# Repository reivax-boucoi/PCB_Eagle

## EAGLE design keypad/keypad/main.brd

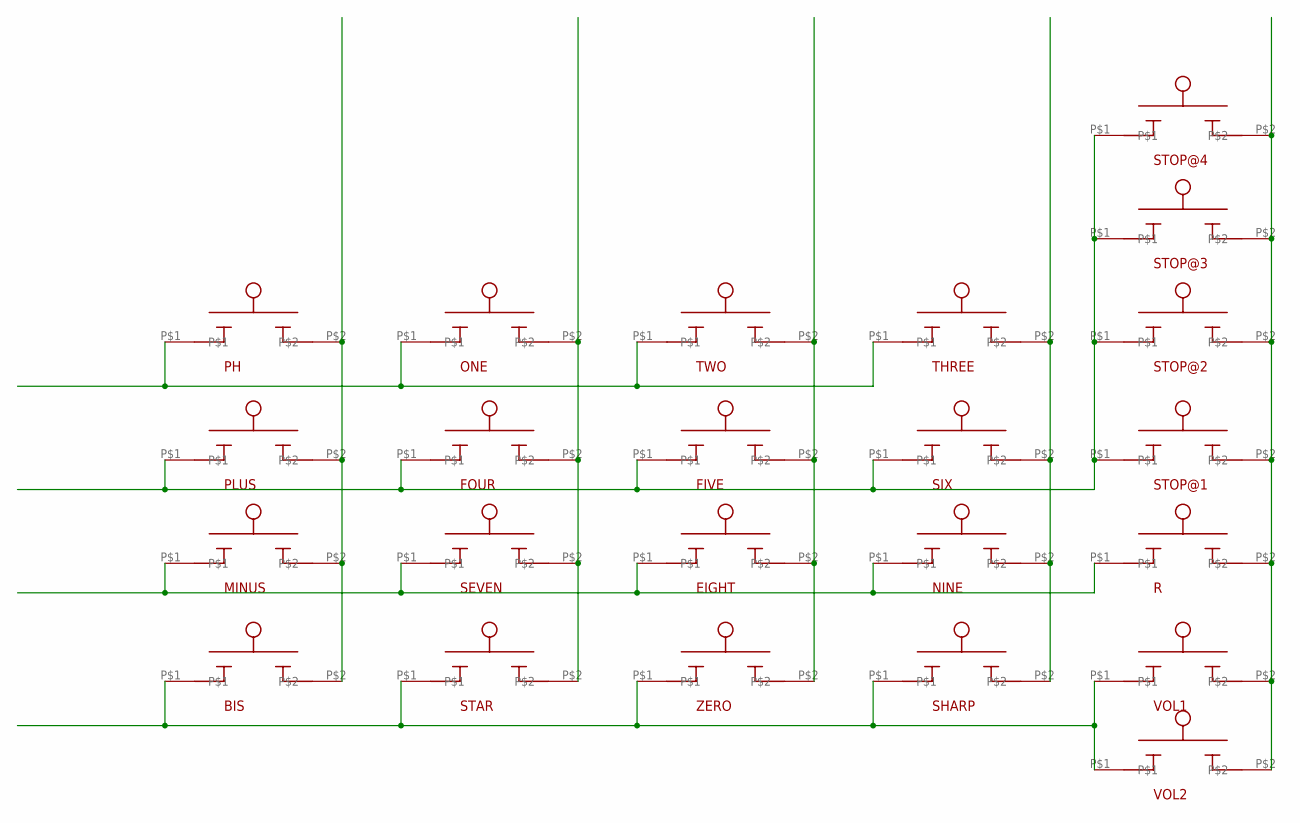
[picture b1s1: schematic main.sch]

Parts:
BIS: MEMBRANE_BUTTON
EIGHT: MEMBRANE_BUTTON
FIVE: MEMBRANE_BUTTON
FOUR: MEMBRANE_BUTTON
MINUS: MEMBRANE_BUTTON
NINE: MEMBRANE_BUTTON
ONE: MEMBRANE_BUTTON
PH: MEMBRANE_BUTTON
PLUS: MEMBRANE_BUTTON
R: MEMBRANE_BUTTON
SEVEN: MEMBRANE_BUTTON
SHARP: MEMBRANE_BUTTON
SIX: MEMBRANE_BUTTON
STAR: MEMBRANE_BUTTON
STOP@1, STOP@2, STOP@3, STOP@4: MEMBRANE_BUTTON
THREE: MEMBRANE_BUTTON
TWO: MEMBRANE_BUTTON
VOL1, VOL2: MEMBRANE_BUTTON
ZERO: MEMBRANE_BUTTON

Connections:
unnamed: ONE.P$1, PH.P$1, THREE.P$1, TWO.P$1
unnamed: FIVE.P$1, FOUR.P$1, PLUS.P$1, SIX.P$1, STOP@1.P$1, STOP@2.P$1, STOP@3.P$1, STOP@4.P$1
unnamed: EIGHT.P$1, MINUS.P$1, NINE.P$1, R.P$1, SEVEN.P$1
unnamed: BIS.P$2, MINUS.P$2, PH.P$2, PLUS.P$2
unnamed: FOUR.P$2, ONE.P$2, SEVEN.P$2, STAR.P$2
unnamed: EIGHT.P$2, FIVE.P$2, TWO.P$2, ZERO.P$2
unnamed: NINE.P$2, SHARP.P$2, SIX.P$2, THREE.P$2
unnamed: R.P$2, STOP@1.P$2, STOP@2.P$2, STOP@3.P$2, STOP@4.P$2, VOL1.P$2, VOL2.P$2
unnamed: BIS.P$1, SHARP.P$1, STAR.P$1, VOL1.P$1, VOL2.P$1, ZERO.P$1

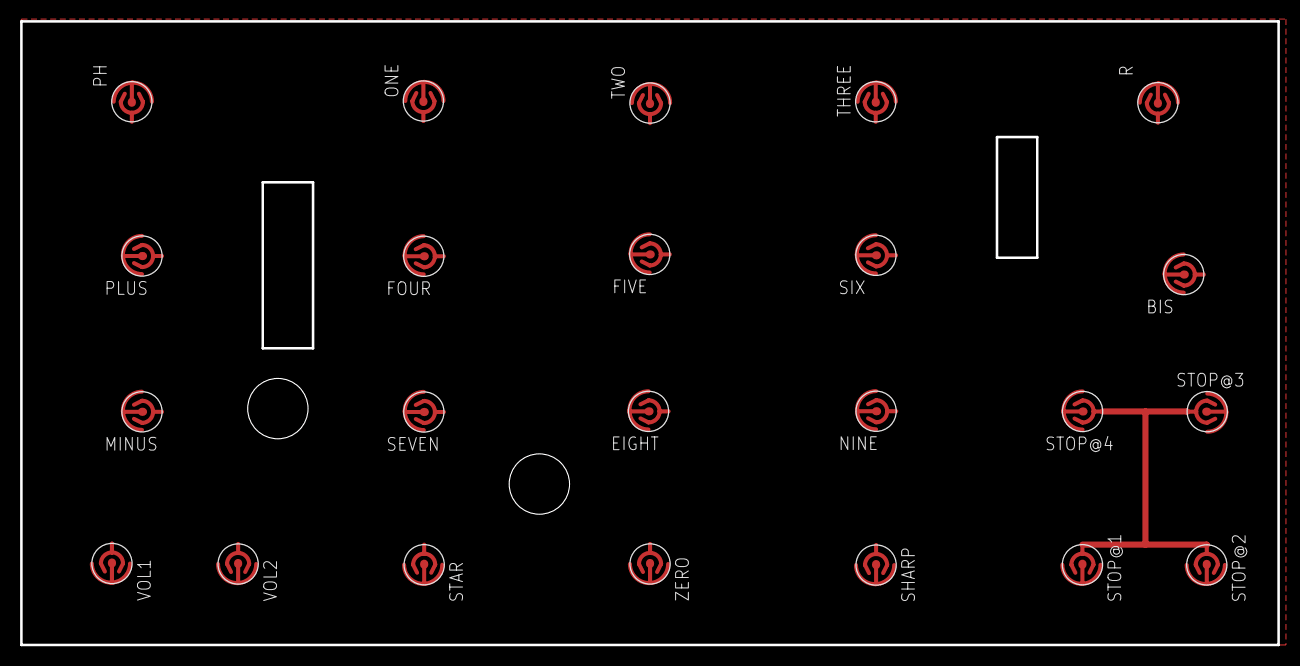
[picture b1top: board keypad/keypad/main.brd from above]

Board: 2 copper layers, 125.0 x 62.0 mm, 23 parts (0 on the bottom side), 9 nets.

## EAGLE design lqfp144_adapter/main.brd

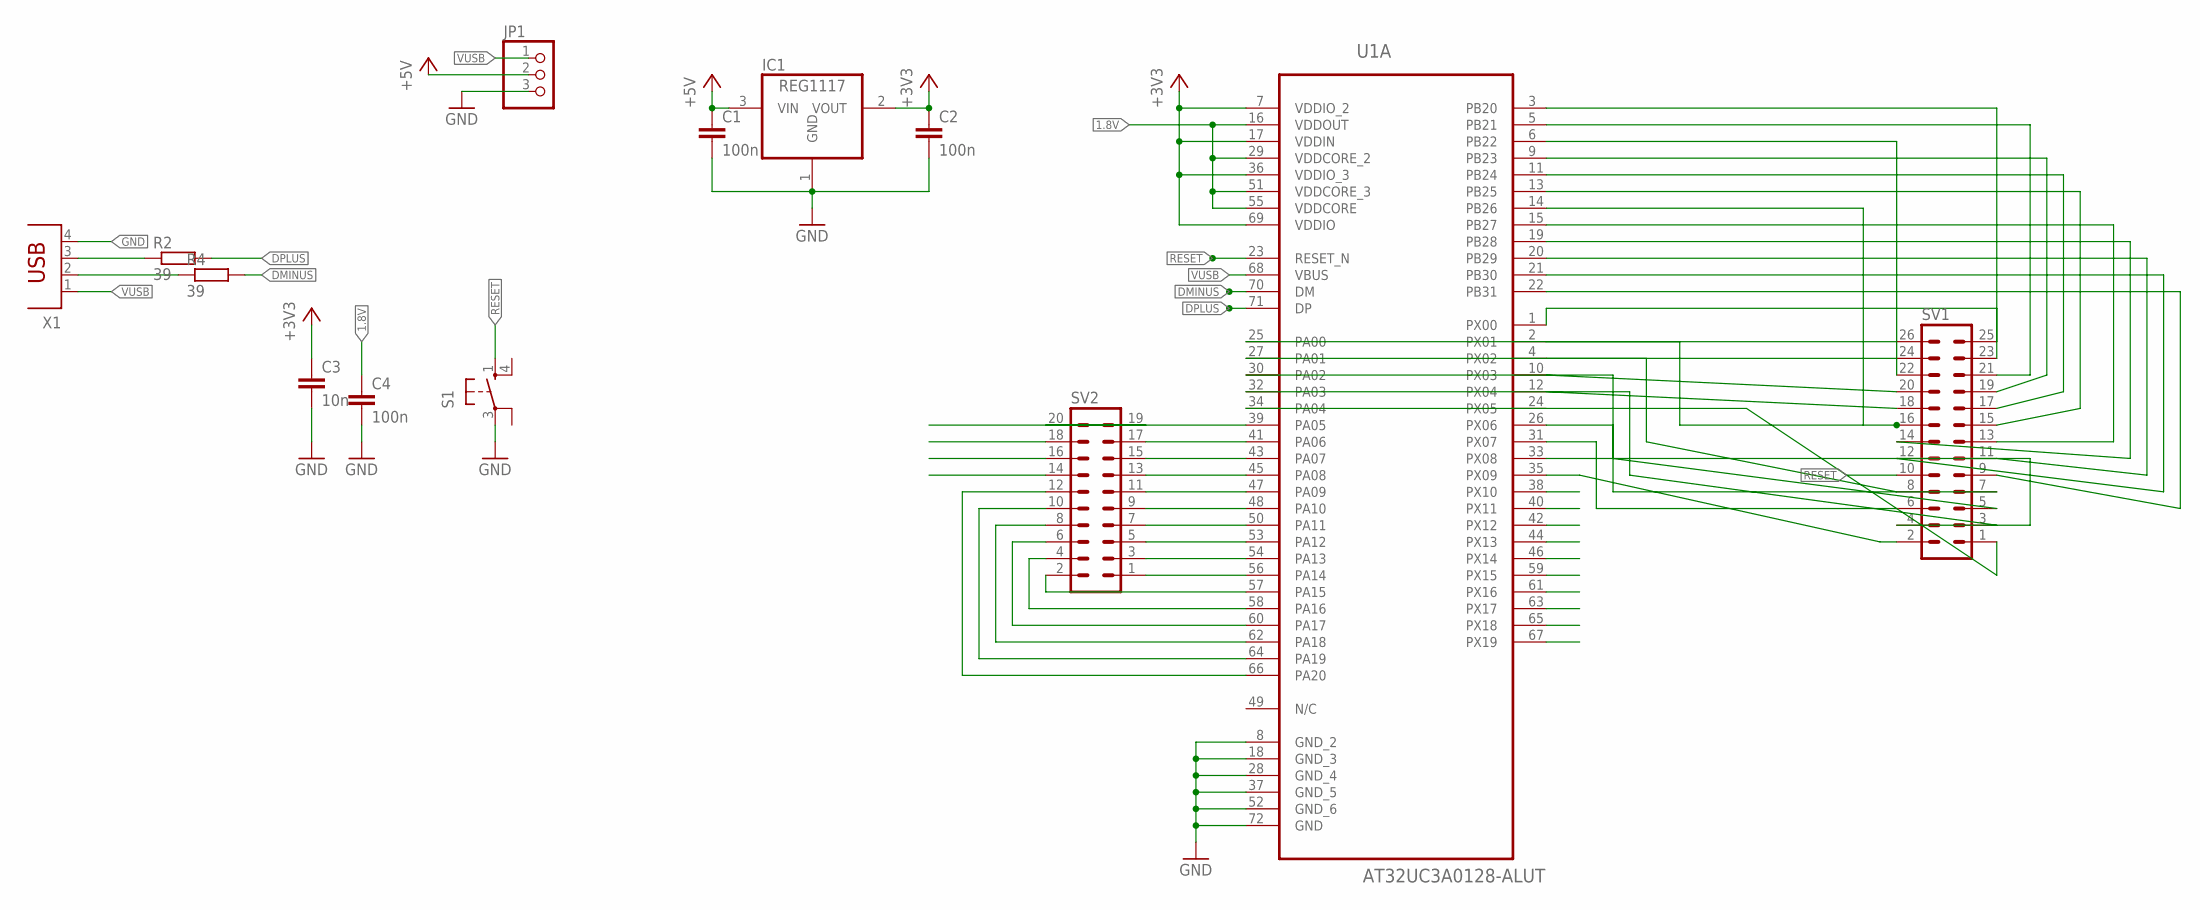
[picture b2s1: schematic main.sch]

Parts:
C1, C2, C4: 100n; C050-025X075
C3: 10n; C050-025X075
IC1: REG1117; SOT223
JP1: PINHD-1X3; 1X03
R2, R4: 39; 0207/10
S1: 10-XX; B3F-10XX
SV1: MA13-2
SV2: MA10-2
U1: AT32UC3A0128-ALUT; QFP50P2200X2200X160-144N
X1: PN61729

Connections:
1.8V: C4.1, U1.16 (VDDOUT), U1.29 (VDDCORE_2), U1.51 (VDDCORE_3), U1.55 (VDDCORE)
+3V3: C2.1, C3.1, IC1.2 (VOUT), U1.7 (VDDIO_2), U1.17 (VDDIN), U1.36 (VDDIO_3), U1.69 (VDDIO)
+5V: C1.1, IC1.3 (VIN), JP1.2
B$1: SV2.14, SV2.16, SV2.18, SV2.19, U1.38 (PX10), U1.40 (PX11), U1.42 (PX12), U1.44 (PX13), U1.46 (PX14), U1.59 (PX15), U1.61 (PX16), U1.63 (PX17), U1.65 (PX18), U1.67 (PX19)
DMINUS: R4.2, U1.70 (DM)
DPLUS: R2.2, U1.71 (DP)
GND: C1.2, C2.2, C3.2, C4.2, IC1.1 (GND), JP1.3, S1.3, U1.8 (GND_2), U1.18 (GND_3), U1.28 (GND_4), U1.37 (GND_5), U1.52 (GND_6), U1.72 (GND), X1.4
unnamed: SV1.25, U1.1 (PX00)
unnamed: SV1.26, U1.2 (PX01)
unnamed: SV1.23, U1.3 (PB20)
unnamed: SV1.21, U1.5 (PB21)
unnamed: SV1.24, U1.4 (PX02)
unnamed: SV1.20, U1.10 (PX03)
unnamed: SV1.22, U1.6 (PB22)
unnamed: SV1.19, U1.9 (PB23)
unnamed: SV1.17, U1.11 (PB24)
unnamed: SV1.18, U1.12 (PX04)
unnamed: SV1.15, U1.13 (PB25)
unnamed: SV1.16, U1.14 (PB26), U1.25 (PA00)
unnamed: SV1.13, U1.15 (PB27)
unnamed: SV1.14, U1.19 (PB28)
unnamed: SV1.11, U1.20 (PB29)
unnamed: SV1.12, U1.21 (PB30)
unnamed: SV1.9, U1.22 (PB31)
unnamed: SV1.7, U1.26 (PX06)
unnamed: SV1.8, U1.27 (PA01)
unnamed: SV1.5, U1.30 (PA02)
unnamed: SV1.3, U1.32 (PA03)
unnamed: SV1.1, U1.34 (PA04)
unnamed: SV1.6, U1.31 (PX07)
unnamed: SV1.4, U1.33 (PX08)
unnamed: SV1.2, U1.35 (PX09)
unnamed: R2.1, X1.3
unnamed: SV2.12, U1.66 (PA20)
unnamed: R4.1, X1.2
unnamed: SV2.10, U1.64 (PA19)
unnamed: SV2.8, U1.62 (PA18)
unnamed: SV2.6, U1.60 (PA17)
unnamed: SV2.4, U1.58 (PA16)
unnamed: SV2.2, U1.57 (PA15)
unnamed: SV2.1, U1.56 (PA14)
unnamed: SV2.3, U1.54 (PA13)
unnamed: SV2.5, U1.53 (PA12)
unnamed: SV2.7, U1.50 (PA11)
unnamed: SV2.9, U1.48 (PA10)
unnamed: SV2.11, U1.47 (PA09)
unnamed: SV2.13, U1.45 (PA08)
unnamed: SV2.15, U1.43 (PA07)
unnamed: SV2.17, U1.41 (PA06)
unnamed: SV2.20, U1.39 (PA05)
RESET: S1.1 (S), SV1.10, U1.23 (RESET_N)
VDDANA: U1.81 (VDDANA)
VDDCORE: U1.138 (VDDCORE)
VDDIO: U1.116 (VDDIO)
VDDIO_2: U1.92 (VDDIO_2)
VDDIO_3: U1.93 (VDDIO_3)
VDDIO_4: U1.108 (VDDIO_4)
VDDPLL: U1.84 (VDDPLL)
VUSB: JP1.1, U1.68 (VBUS), X1.1

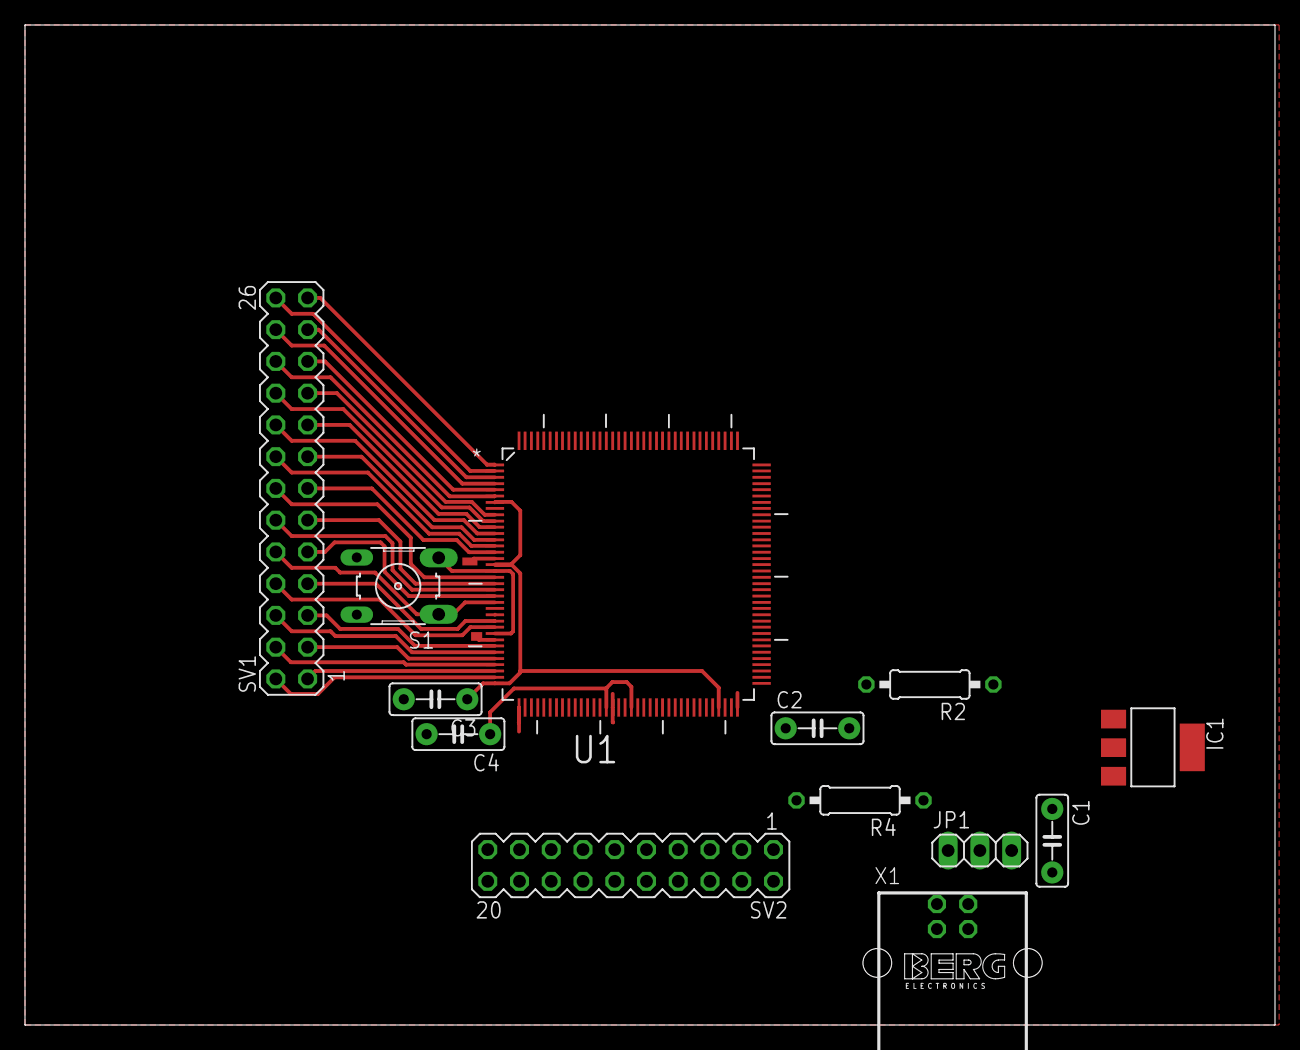
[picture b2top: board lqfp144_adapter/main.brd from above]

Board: 2 copper layers, 100.0 x 80.0 mm, 13 parts (0 on the bottom side), 52 nets.

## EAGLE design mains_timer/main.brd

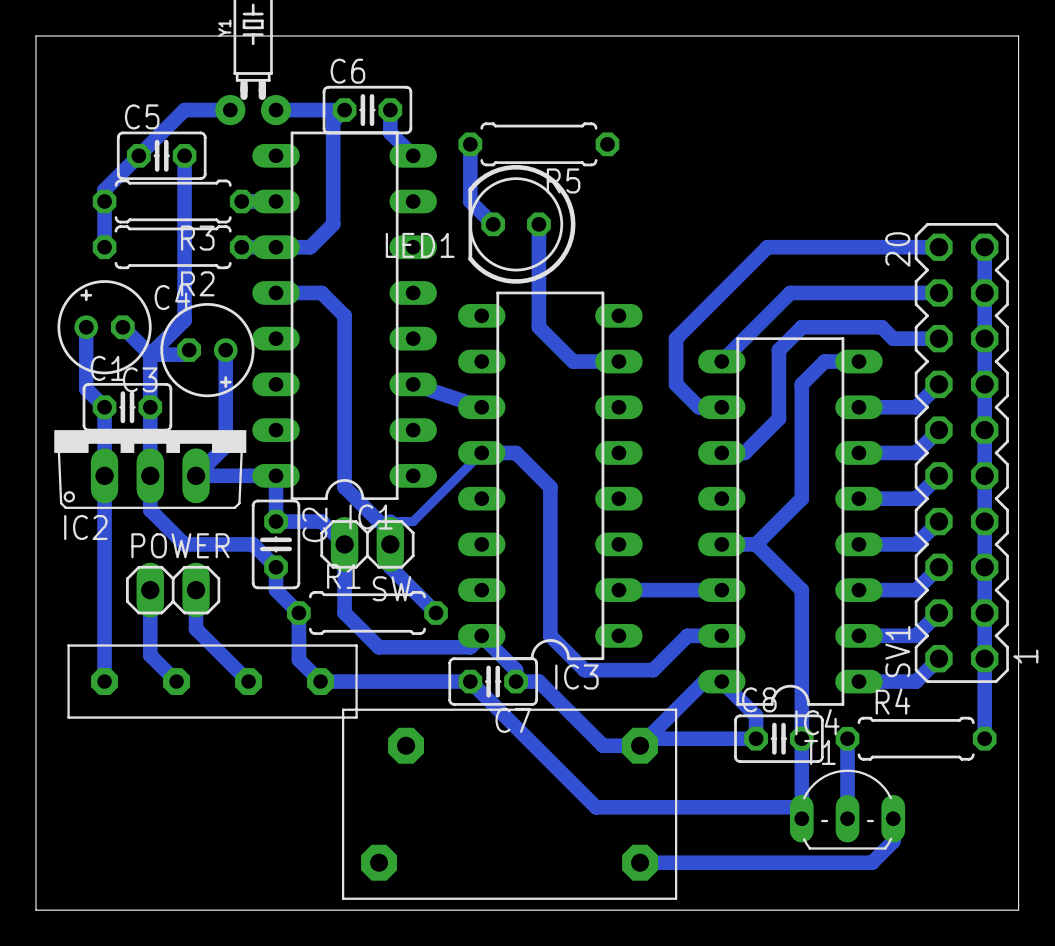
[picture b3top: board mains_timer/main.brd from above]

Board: 2 copper layers, 54.6 x 48.6 mm, 25 parts (0 on the bottom side), 26 nets.

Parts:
C1: 100u; C025-025X050
C2, C7, C8: 100n; C025-025X050
C3: 100u; E2-5
C4: 100n; E2-5
C5, C6: 33p; C025-025X050
IC1, IC3: 4060N; DIL16
IC2: 7812TV; TO220V
IC4: 4017N; DIL16
LED1: LED5MM
POWER: 1X02
R1: 22k; 0207/7
R2: 10M; 0207/7
R3: 330k; 0207/7
R4: 0207/7
R5: 500; 0207/7
SV1: MA10-2
SW: 1X02
T1: 2N2222; TO92-EBC-OVAL
U$2: KBP205GK; KBP205G
U$3: 835-1A_RELAY12V; 835-1A_RELAY_12V
Y1: 32.768kHz; CRYSTAL-PTH-2X6-CYL

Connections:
12V: C2.1, C3.+, C7.1, C8.1, IC1.16, IC2.3, IC3.16, IC4.16, SW.2, U$3.P$1
GND: C1.2, C2.2, C3.-, C4.-, C5.2, C6.2, C7.2, C8.2, IC1.8, IC2.2, IC3.8, IC4.8, IC4.13, R1.1, R5.1, T1.E, U$2.-
unnamed: POWER.2, U$2.AC@2
unnamed: POWER.1, U$2.AC@1
unnamed: IC1.12, IC3.12, IC4.15, R1.2, SW.1
unnamed: IC1.10, R3.1
unnamed: C6.1, IC1.11, R2.1, Y1.2
unnamed: IC1.3, IC3.11
unnamed: C5.1, R2.2, R3.2, Y1.1
unnamed: IC3.2, IC4.14
unnamed: IC4.11, SV1.16
unnamed: IC4.9, SV1.18
unnamed: IC4.6, SV1.12
unnamed: IC4.5, SV1.10
unnamed: IC4.1, SV1.2
unnamed: IC4.10, SV1.20
unnamed: IC4.7, SV1.14
unnamed: IC4.4, SV1.8
unnamed: IC4.2, SV1.4
unnamed: IC4.3, SV1.6
unnamed: R4.2, SV1.1, SV1.3, SV1.5, SV1.7, SV1.9, SV1.11, SV1.13, SV1.15, SV1.17, SV1.19
unnamed: R4.1, T1.B
unnamed: T1.C, U$3.P$2
unnamed: LED1.K, R5.2
unnamed: IC3.7, LED1.A
VDD: C1.1, C4.+, IC2.1, U$2.+

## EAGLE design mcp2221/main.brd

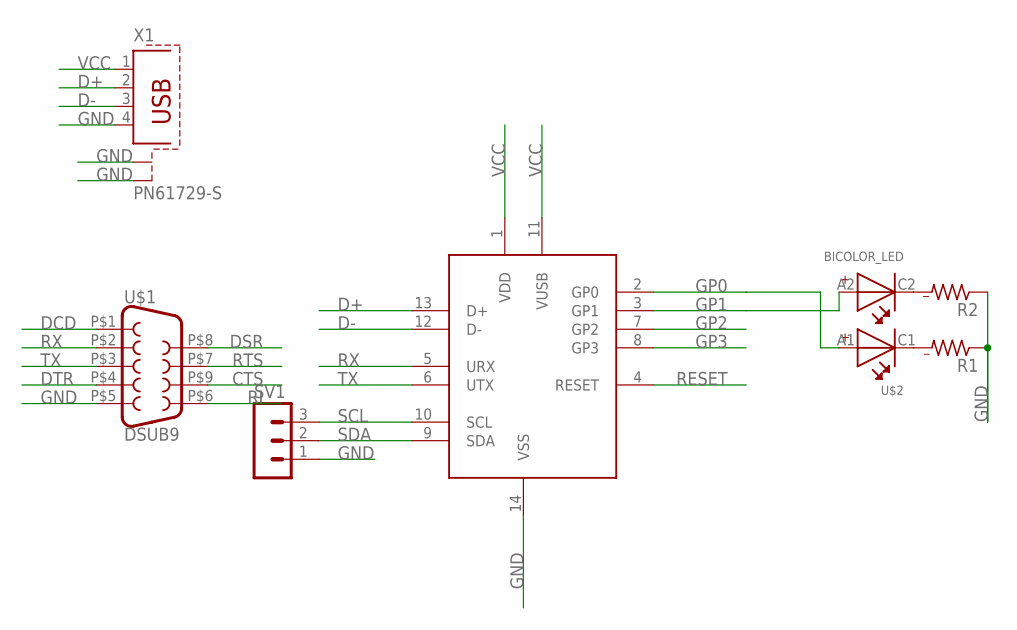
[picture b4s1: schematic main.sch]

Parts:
BR1: MCP2221A; DIP14
R1, R2: R-US_M0805; M0805
SV1: MA03-1
U$1: DSUB9; DSUB9_EDGECARD
U$2: BICOLOR_LED
X1: PN61729-S

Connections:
CTS: U$1.P$9 (CTS)
D+: BR1.13 (D+), X1.2
D-: BR1.12 (D-), X1.3
DCD: U$1.P$1 (DCD)
DSR: U$1.P$8 (DSR)
DTR: U$1.P$4 (DTR)
GND: BR1.14 (VSS), R1.1, R2.1, SV1.1, U$1.P$5 (GND), X1.4, X1.S1, X1.S2
GP0: BR1.2 (GP0), U$2.A1
GP1: BR1.3 (GP1), U$2.A2
GP2: BR1.7 (GP2)
GP3: BR1.8 (GP3)
unnamed: R1.2, U$2.C1
unnamed: R2.2, U$2.C2
RESET: BR1.4 (RESET)
RI: U$1.P$6 (RI)
RTS: U$1.P$7 (RTS)
RX: BR1.5 (URX), U$1.P$2 (RXD)
SCL: BR1.10 (SCL), SV1.3
SDA: BR1.9 (SDA), SV1.2
TX: BR1.6 (UTX), U$1.P$3 (TXD)
VCC: BR1.1 (VDD), BR1.11 (VUSB), X1.1

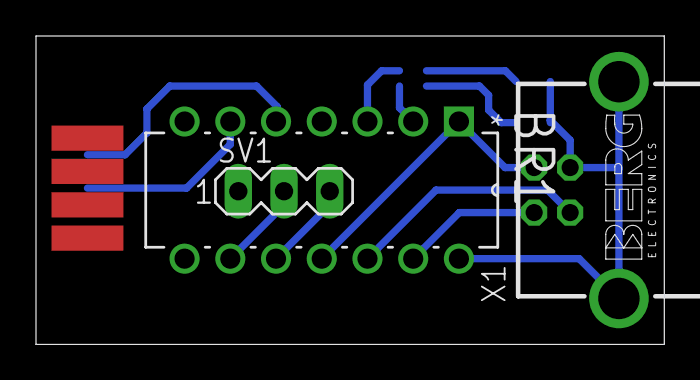
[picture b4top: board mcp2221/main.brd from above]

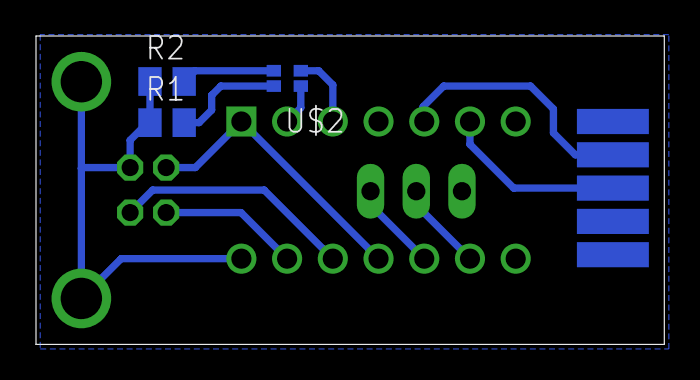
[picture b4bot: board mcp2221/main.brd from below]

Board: 2 copper layers, 34.9 x 17.1 mm, 7 parts (4 on the bottom side), 12 nets.

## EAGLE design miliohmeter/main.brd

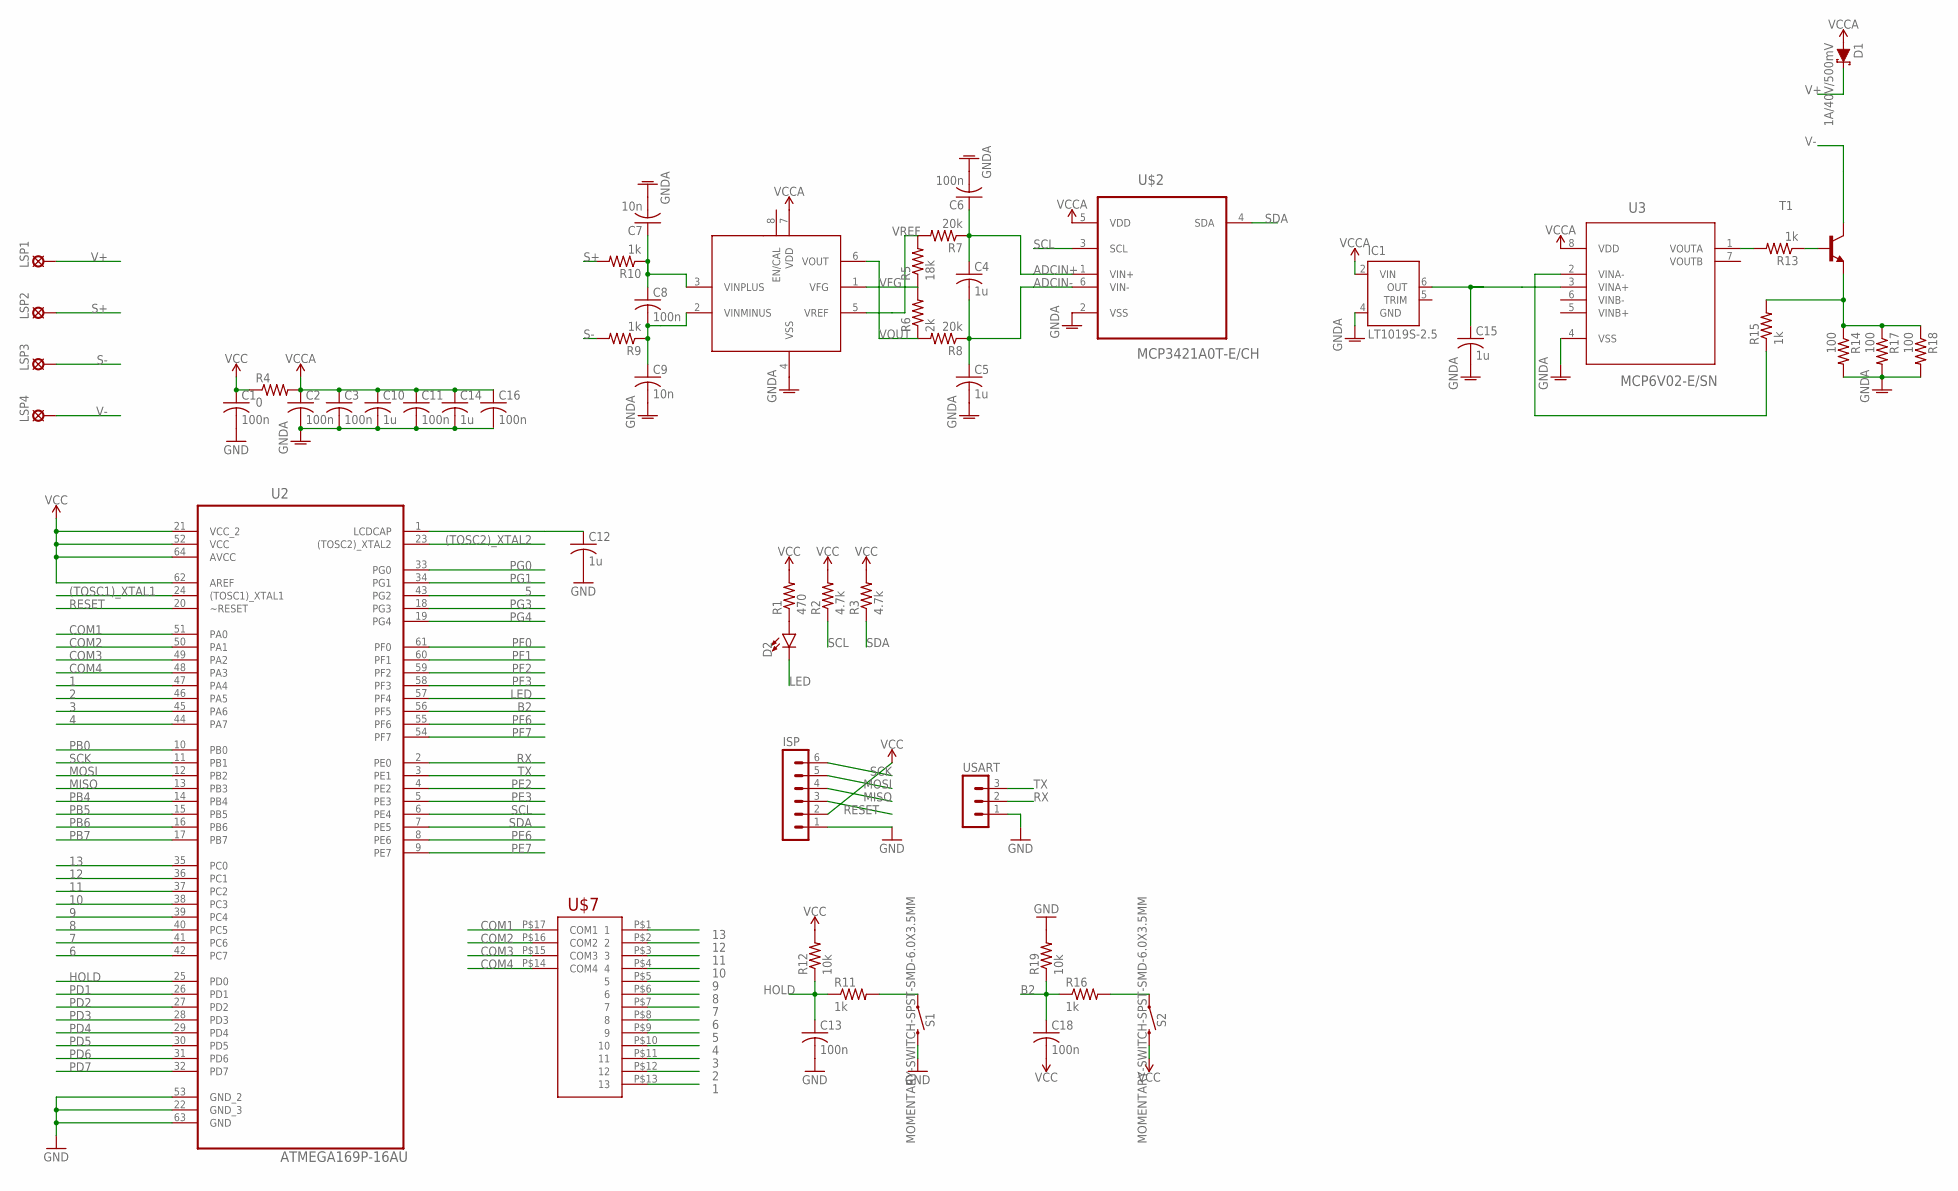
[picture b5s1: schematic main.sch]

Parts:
C1, C2, C3, C6, C8, C11, C13, C16, C18: 100n; C0603
C4, C5, C10, C12, C14, C15: 1u; C0603
C7, C9: 10n; C0603
D1: 1A/40V/500mV; SMA-DIODE
D2: LED5MM; LED_5MM
IC1: LT1019S-2.5; SOIC8
ISP: MA06-1
LSP1, LSP2, LSP3, LSP4: MCS08
R1: 470; R0603
R2, R3: 4.7k; R0603
R4: 0; 0309/12
R5: 18k; R0603
R6: 2k; R0603
R7, R8: 20k; R0603
R9, R10, R11, R13, R15, R16: 1k; R0603
R12, R19: 10k; R0603
R14, R17, R18: 100; R0603
S1, S2: MOMENTARY-SWITCH-SPST-SMD-6.0X3.5MM; TACTILE_SWITCH_SMD_6.0X3.5MM
T1: MMBT3904LT1-NPN-SOT23-BEC; SOT23-BEC
U2: ATMEGA169P-16AU; QFP80P1600X1600X120-64N
U3: MCP6V02-E/SN; SOIC127P600X175-8N
U$2: MCP3421A0T-E/CH; SOT95P270X145-6N
U$3: MCP6N11; SOIC8
U$7: GDC0570_LCD
USART: MA03-1

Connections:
1: U2.47 (PA4), U$7.P$13 (13)
2: U2.46 (PA5), U$7.P$12 (12)
3: U2.45 (PA6), U$7.P$11 (11)
4: U2.44 (PA7), U$7.P$10 (10)
5: U2.43 (PG2), U$7.P$9 (9)
6: U2.42 (PC7), U$7.P$8 (8)
7: U2.41 (PC6), U$7.P$7 (7)
8: U2.40 (PC5), U$7.P$6 (6)
9: U2.39 (PC4), U$7.P$5 (5)
10: U2.38 (PC3), U$7.P$4 (4)
11: U2.37 (PC2), U$7.P$3 (3)
12: U2.36 (PC1), U$7.P$2 (2)
13: U2.35 (PC0), U$7.P$1 (1)
ADCIN+: C4.1, C6.1, R7.1, U$2.1 (VIN+)
ADCIN-: C4.2, C5.1, R8.1, U$2.6 (VIN-)
B2: C18.1, R16.1, R19.1, U2.56 (PF5)
COM1: U2.51 (PA0), U$7.P$17 (COM1)
COM2: U2.50 (PA1), U$7.P$16 (COM2)
COM3: U2.49 (PA2), U$7.P$15 (COM3)
COM4: U2.48 (PA3), U$7.P$14 (COM4)
GND: C1.2, C12.2, C13.2, ISP.1, R19.2, S1.2, U2.22 (GND_3), U2.53 (GND_2), U2.63 (GND), USART.1; also elsewhere on the board
GNDA: C2.2, C3.2, C5.2, C6.2, C7.2, C9.2, C10.2, C11.2, C14.2, C15.2, C16.2, IC1.4 (GND), R14.2, R17.2, R18.2, U3.4 (VSS), U$2.2 (VSS), U$3.4 (VSS)
HOLD: C13.1, R11.1, R12.1, U2.25 (PD0)
LCDCAP: C12.1, U2.1 (LCDCAP)
LED: D2.K (C), U2.57 (PF4)
MISO: ISP.4, U2.13 (PB3)
MOSI: ISP.5, U2.12 (PB2)
N1: R11.2, S1.1
N2: R16.2, S2.1
unnamed: C15.1, IC1.6 (OUT), U3.3 (VINA+)
unnamed: R14.1, R15.2, R17.1, R18.1, T1.E
unnamed: C8.2, C9.1, R9.1, U$3.2 (VINMINUS)
unnamed: C7.1, C8.1, R10.1, U$3.3 (VINPLUS)
unnamed: D2.A, R1.1
unnamed: R13.2, U3.1 (VOUTA)
unnamed: R13.1, T1.B
unnamed: R15.1, U3.2 (VINA-)
PB0: U2.10 (PB0)
PB4: U2.14 (PB4)
PB5: U2.15 (PB5)
PB6: U2.16 (PB6)
PB7: U2.17 (PB7)
PD1: U2.26 (PD1)
PD2: U2.27 (PD2)
PD3: U2.28 (PD3)
PD4: U2.29 (PD4)
PD5: U2.30 (PD5)
PD6: U2.31 (PD6)
PD7: U2.32 (PD7)
PE2: U2.4 (PE2)
PE3: U2.5 (PE3)
PE6: U2.8 (PE6)
PE7: U2.9 (PE7)
PF0: U2.61 (PF0)
PF1: U2.60 (PF1)
PF2: U2.59 (PF2)
PF3: U2.58 (PF3)
PF6: U2.55 (PF6)
PF7: U2.54 (PF7)
PG0: U2.33 (PG0)
PG1: U2.34 (PG1)
PG3: U2.18 (PG3)
PG4: U2.19 (PG4)
RESET: ISP.3, U2.20 (~RESET)
RX: U2.2 (PE0), USART.2; also elsewhere on the board
S+: LSP2.MP, R10.2
S-: LSP3.MP, R9.2
SCK: ISP.6, U2.11 (PB1)
SCL: R2.1, U2.6 (PE4), U$2.3 (SCL)
SDA: R3.1, U2.7 (PE5), U$2.4 (SDA)
TX: U2.3 (PE1), USART.3; also elsewhere on the board
V+: D1.C, LSP1.MP
V-: LSP4.MP, T1.C
VCC: C1.1, C18.2, ISP.2, R1.2, R2.2, R3.2, R4.1, R12.2, S2.2, U2.21 (VCC_2), U2.52 (VCC), U2.62 (AREF), U2.64 (AVCC); also elsewhere on the board
VCCA: C2.1, C3.1, C10.1, C11.1, C14.1, C16.1, D1.A, IC1.2 (VIN), R4.2, U3.8 (VDD), U$2.5 (VDD), U$3.7 (VDD)
VFG: R5.1, R6.2, U$3.1 (VFG)
VOUT: R6.1, R8.2, U$3.6 (VOUT)
VREF: R5.2, R7.2, U$3.5 (VREF)

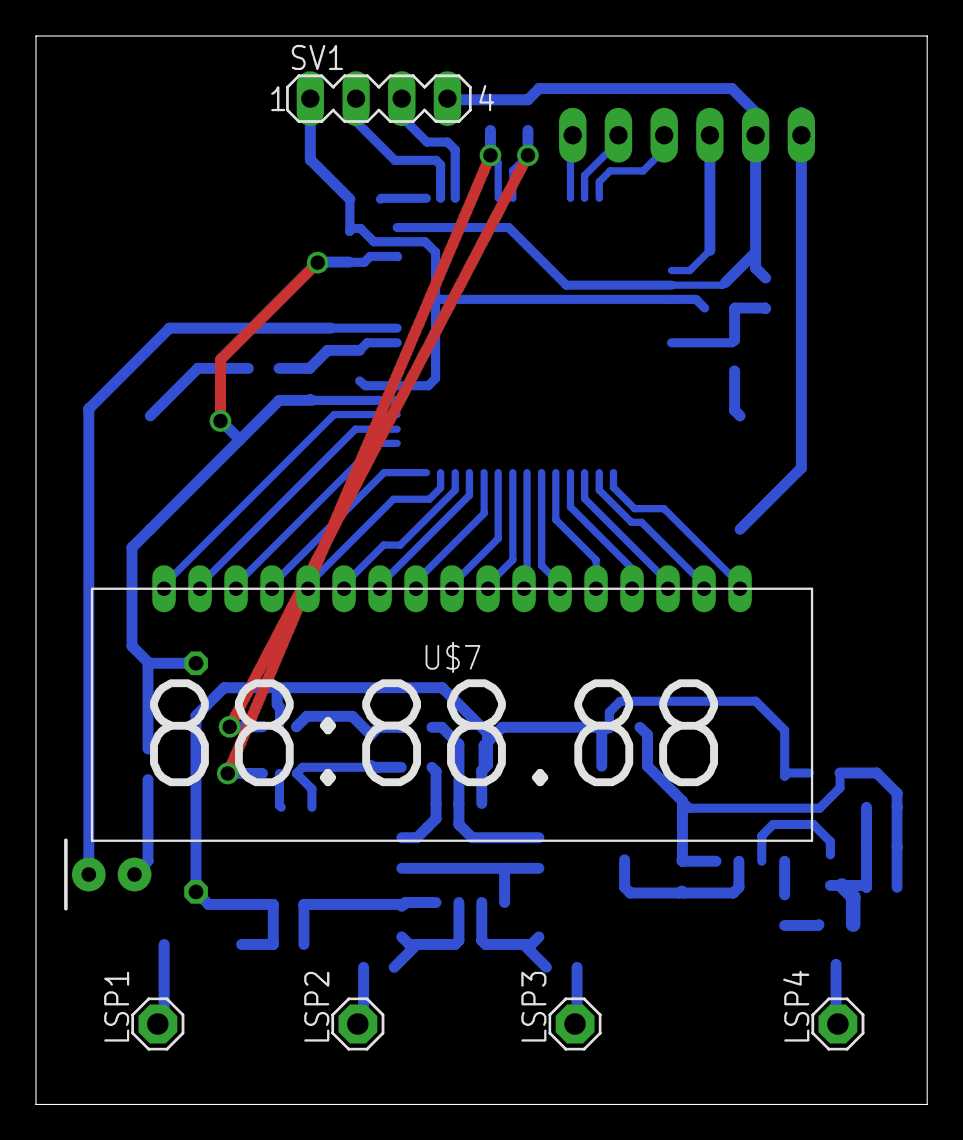
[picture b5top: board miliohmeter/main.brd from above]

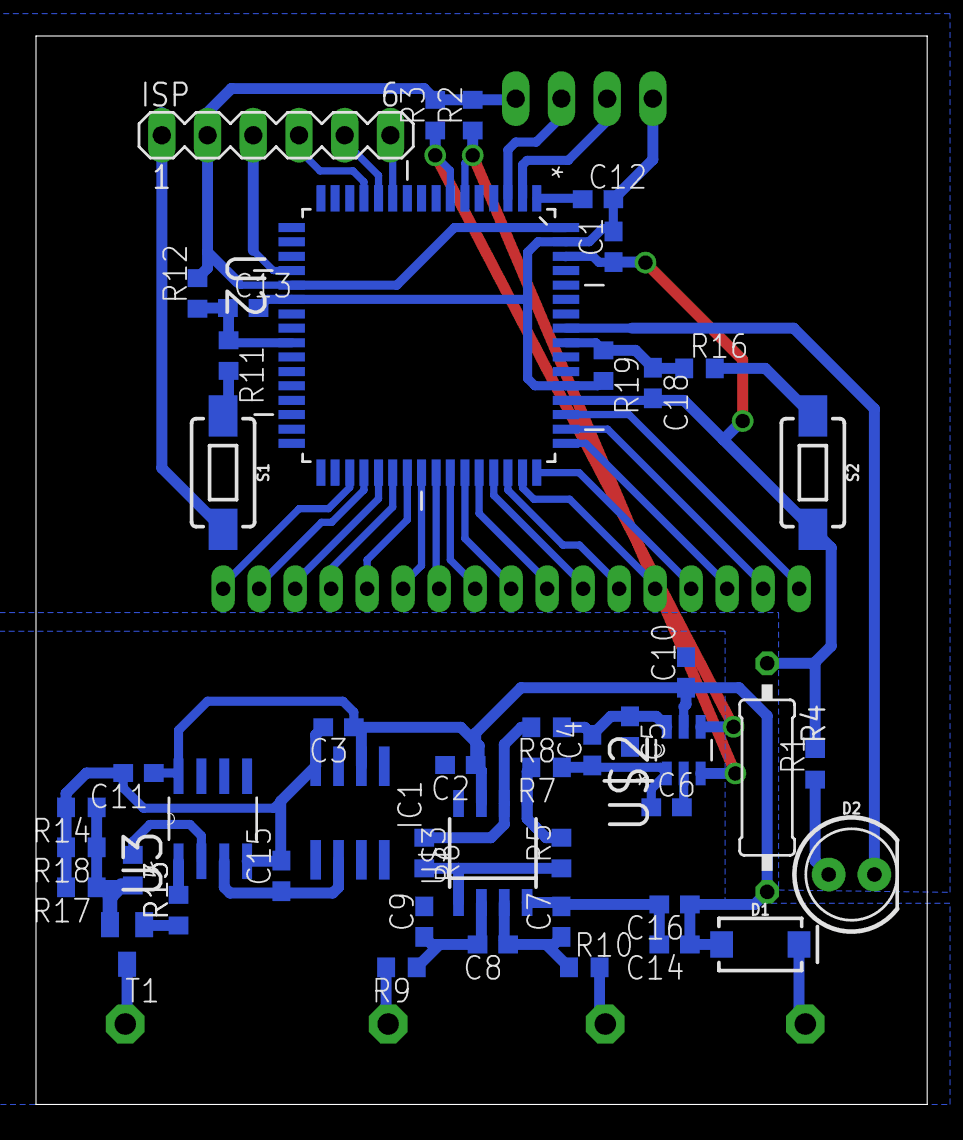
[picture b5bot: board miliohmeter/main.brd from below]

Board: 2 copper layers, 49.5 x 59.4 mm, 53 parts (47 on the bottom side), 52 nets.

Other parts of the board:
SV1: MA04-1

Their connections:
GND: SV1.1; also elsewhere on the board
RX: SV1.2; also elsewhere on the board
TX: SV1.3; also elsewhere on the board
VCC: SV1.4; also elsewhere on the board

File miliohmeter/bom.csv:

"Qty";"Value";"Device";"Package";"Parts";"Description";"";
"1";"";"LED5MM";"LED_5MM";"D2";"LED (Generic)";"";
"1";"";"MA04-1";"MA04-1";"USART";"PIN HEADER";"";
"1";"";"MMBT3904LT1-NPN-SOT23-BEC";"SOT23-BEC";"T1";"NPN Transistror";"";
"1";"";"PINHD-1X2";"1X02";"PWR";"PIN HEADER";"";
"1";"";"PINHD-1X6";"1X06";"ISP";"PIN HEADER";"";
"1";"0";"R-US_0309/12";"0309/12";"R4";"RESISTOR, American symbol";"";
"1";"0";"R-US_R0603";"R0603";"R21";"RESISTOR, American symbol";"";
"4";"100";"R-US_R0603";"R0603";"R14, R17, R18, R20";"RESISTOR, American symbol";"";
"12";"100n";"C-USC0603";"C0603";"C1, C2, C3, C6, C8, C11, C13, C16, C17, C18, C19, C20";"CAPACITOR, American symbol";"";
"2";"10k";"R-US_R0603";"R0603";"R12, R19";"RESISTOR, American symbol";"";
"2";"10n";"C-USC0603";"C0603";"C7, C9";"CAPACITOR, American symbol";"";
"1";"18k";"R-US_R0603";"R0603";"R5";"RESISTOR, American symbol";"";
"2";"1A/40V/500mV";"DIODE-SCHOTTKY-SS14";"SMA-DIODE";"D1, D3";"Schottky diode";"";
"6";"1k";"R-US_R0603";"R0603";"R9, R10, R11, R13, R15, R16";"RESISTOR, American symbol";"";
"6";"1u";"C-USC0603";"C0603";"C4, C5, C10, C12, C14, C15";"CAPACITOR, American symbol";"";
"2";"20k";"R-US_R0603";"R0603";"R7, R8";"RESISTOR, American symbol";"";
"1";"2k";"R-US_R0603";"R0603";"R6";"RESISTOR, American symbol";"";
"2";"4.7k";"R-US_R0603";"R0603";"R2, R3";"RESISTOR, American symbol";"";
"1";"470";"R-US_R0603";"R0603";"R1";"RESISTOR, American symbol";"";
"1";"7805TV";"7805TV";"TO220V";"REG1";"Positive VOLTAGE REGULATOR";"";
"1";"ATMEGA169P-16AU";"ATMEGA169P-16AU";"QFP80P1600X1600X120-64N";"U2";"8-bit Microcontroller with 16K Bytes In-System Programmable Flash";"";
"1";"GDC0570_LCD";"GDC0570_LCD";"GDC0570_LCD";"LCD1";"";"";
"1";"LT1019S-2.5";"LT1019S-2.5";"SOIC8";"IC1";"Precision Voltage Reference";"";
"1";"MCP3421A0T-E/CH";"MCP3421A0T-E/CH";"SOT95P270X145-6N";"U$2";"Analog-to-Digital Converter";"";
"1";"MCP6N11";"MCP6N11";"SOIC8";"U$3";"";"";
"1";"MCP6V02-E/SN";"MCP6V02-E/SN";"SOIC127P600X175-8N";"U3";"Auto-Zeroed Op Amps";"";
"4";"MCS08";"MCS08";"MCS08";"S+, S-, V+, V-";"SOLDER PAD MC S0,8, drill 1.2 mm, distributor Buerklin, 08F130";"";
"1";"SHORT32";"SHORT32";"SHORT_32";"U$10";"";"";
"1";"b2";"TAC_SWITCHPTH";"TACTILE-PTH";"S2";"Momentary Switch";"";
"1";"hold";"TAC_SWITCHPTH";"TACTILE-PTH";"S1";"Momentary Switch";"";

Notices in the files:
parts and their libraries:
SparkFun-Clocks: Licensing: Creative Commons ShareAlike 4.0 International - https://creativecommons.org/licenses/by-sa/4.0
